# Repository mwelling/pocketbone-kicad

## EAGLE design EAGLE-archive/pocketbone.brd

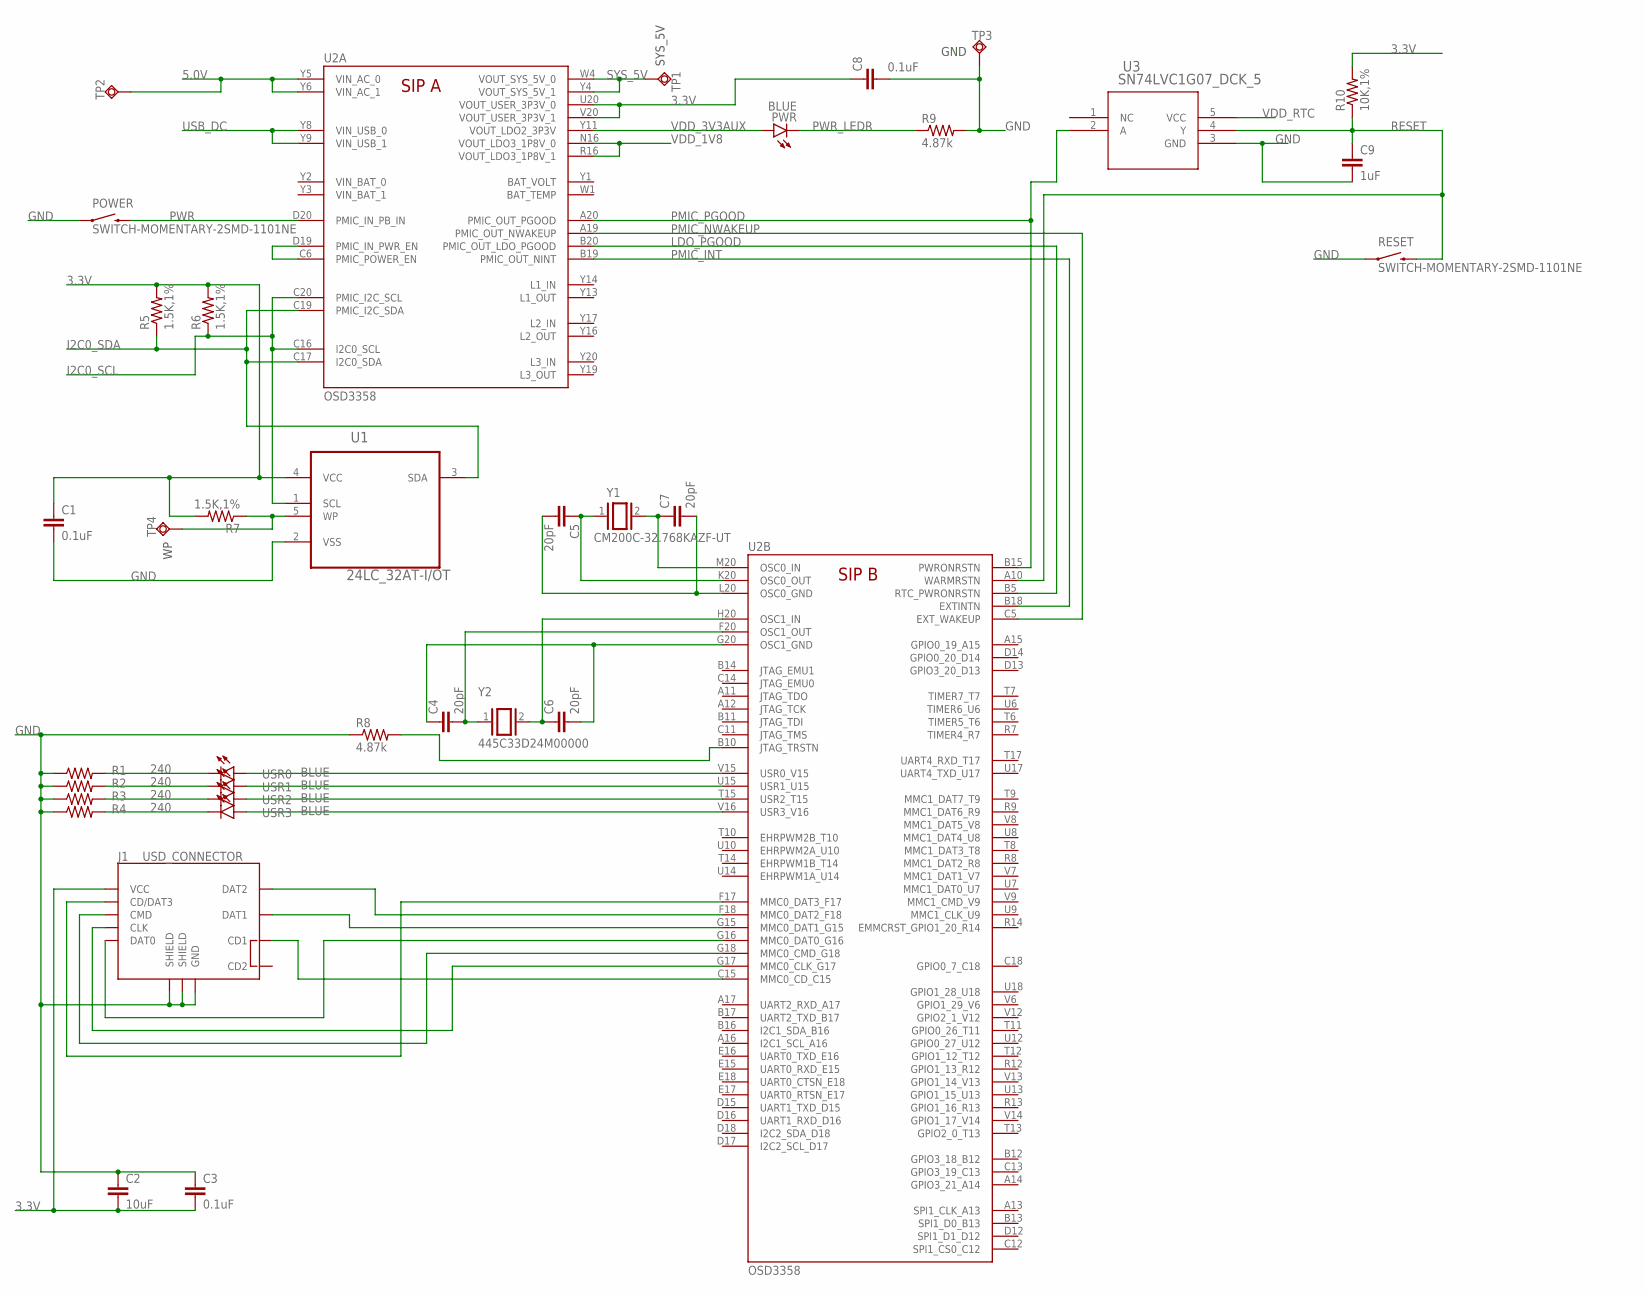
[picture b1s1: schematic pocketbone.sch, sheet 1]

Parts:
C1, C3, C8: 0.1uF; 0402-CAP
C2: 10uF; 0805
C4, C5, C6, C7: 20pF; 0402-CAP
C9: 1uF; 0402-CAP
J1: USD_CONNECTOR; MICRO-SD-SOCKET-PP
POWER: SWITCH-MOMENTARY-2SMD-1101NE; TACTILE-SWITCH-1101NE
PWR: BLUE; LED-0603
R1, R2, R3, R4: 240; 0402-RES
R5, R6, R7: 1.5K,1%; 0402-RES
R8, R9: 4.87k; 0402-RES
R10: 10K,1%; 0402-RES
RESET: SWITCH-MOMENTARY-2SMD-1101NE; TACTILE-SWITCH-1101NE
TP1, TP2, TP3, TP4: TPSQPAD1-17; P1-17
U1: 24LC_32AT-I/OT; SOT95P290X145-5N
U2: OSD3358
U3: SN74LVC1G07_DCK_5; DCK5
USR0, USR1, USR2, USR3: BLUE; LED-0603
Y1: CM200C-32.768KAZF-UT
Y2: 445C33D24M00000

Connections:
3.3V: C1.1, C2.2, C3.2, C8.1, J1.VCC, R5.2, R6.2, R7.2, R10.2, U1.4 (VCC), U2.U20 (VOUT_USER_3P3V_0), U2.V20 (VOUT_USER_3P3V_1); also elsewhere on the board
5.0V: TP2.TP, U2.Y5 (VIN_AC_0), U2.Y6 (VIN_AC_1); also elsewhere on the board
GND: C1.2, C2.1, C3.1, C8.2, C9.2, J1.GND, J1.GND1 (SHIELD), J1.GND3 (SHIELD), POWER.1, R1.1, R2.1, R3.1, R4.1, R8.1, R9.2, RESET.1, TP3.TP, U1.2 (VSS), U3.3 (GND); also elsewhere on the board
I2C0_SCL: R6.1, U1.1 (SCL), U2.C16 (I2C0_SCL), U2.C20 (PMIC_I2C_SCL)
I2C0_SDA: R5.1, U1.3 (SDA), U2.C17 (I2C0_SDA), U2.C19 (PMIC_I2C_SDA)
LDO_PGOOD: U2.B5 (RTC_PWRONRSTN), U2.B20 (PMIC_OUT_LDO_PGOOD)
unnamed: J1.CLK, U2.G17 (MMC0_CLK_G17)
unnamed: J1.CD/DAT3, U2.F17 (MMC0_DAT3_F17)
unnamed: U2.C6 (PMIC_POWER_EN), U2.D19 (PMIC_IN_PWR_EN)
unnamed: C7.1, U2.M20 (OSC0_IN), Y1.2
unnamed: C5.1, U2.K20 (OSC0_OUT), Y1.1
unnamed: R7.1, TP4.TP, U1.5 (WP)
unnamed: C5.2, C7.2, U2.L20 (OSC0_GND)
unnamed: C6.1, U2.H20 (OSC1_IN), Y2.2
unnamed: C4.2, U2.F20 (OSC1_OUT), Y2.1
unnamed: C4.1, C6.2, U2.G20 (OSC1_GND)
unnamed: R8.2, U2.B10 (JTAG_TRSTN)
unnamed: U2.V16 (USR3_V16), USR3.A
unnamed: U2.T15 (USR2_T15), USR2.A
unnamed: U2.U15 (USR1_U15), USR1.A
unnamed: U2.V15 (USR0_V15), USR0.A
unnamed: R1.2, USR0.C
unnamed: R2.2, USR1.C
unnamed: R3.2, USR2.C
unnamed: R4.2, USR3.C
unnamed: J1.DAT1, U2.G15 (MMC0_DAT1_G15)
unnamed: J1.CMD, U2.G18 (MMC0_CMD_G18)
unnamed: J1.CD1, U2.C15 (MMC0_CD_C15)
unnamed: J1.DAT0, U2.G16 (MMC0_DAT0_G16)
NTE: J1.DAT2, U2.F18 (MMC0_DAT2_F18)
PMIC_INT: U2.B18 (EXTINTN), U2.B19 (PMIC_OUT_NINT)
PMIC_NWAKEUP: U2.A19 (PMIC_OUT_NWAKEUP), U2.C5 (EXT_WAKEUP)
PMIC_PGOOD: U2.A20 (PMIC_OUT_PGOOD), U2.B15 (PWRONRSTN), U3.2 (A)
PWR: POWER.2, U2.D20 (PMIC_IN_PB_IN)
PWR_LEDR: PWR.C, R9.1
RESET: C9.1, R10.1, RESET.2, U2.A10 (WARMRSTN), U3.4 (Y)
SYS_5V: TP1.TP, U2.W4 (VOUT_SYS_5V_0), U2.Y4 (VOUT_SYS_5V_1); also elsewhere on the board
USB_DC: U2.Y8 (VIN_USB_0), U2.Y9 (VIN_USB_1); also elsewhere on the board
VDD_1V8: U2.N16 (VOUT_LDO3_1P8V_0), U2.R16 (VOUT_LDO3_1P8V_1); also elsewhere on the board
VDD_3V3AUX: PWR.A, U2.Y11 (VOUT_LDO2_3P3V)
VDD_RTC: U3.5 (VCC); also elsewhere on the board
VIN_BAT_0: U2.Y2 (VIN_BAT_0)
VIN_BAT_1: U2.Y3 (VIN_BAT_1)

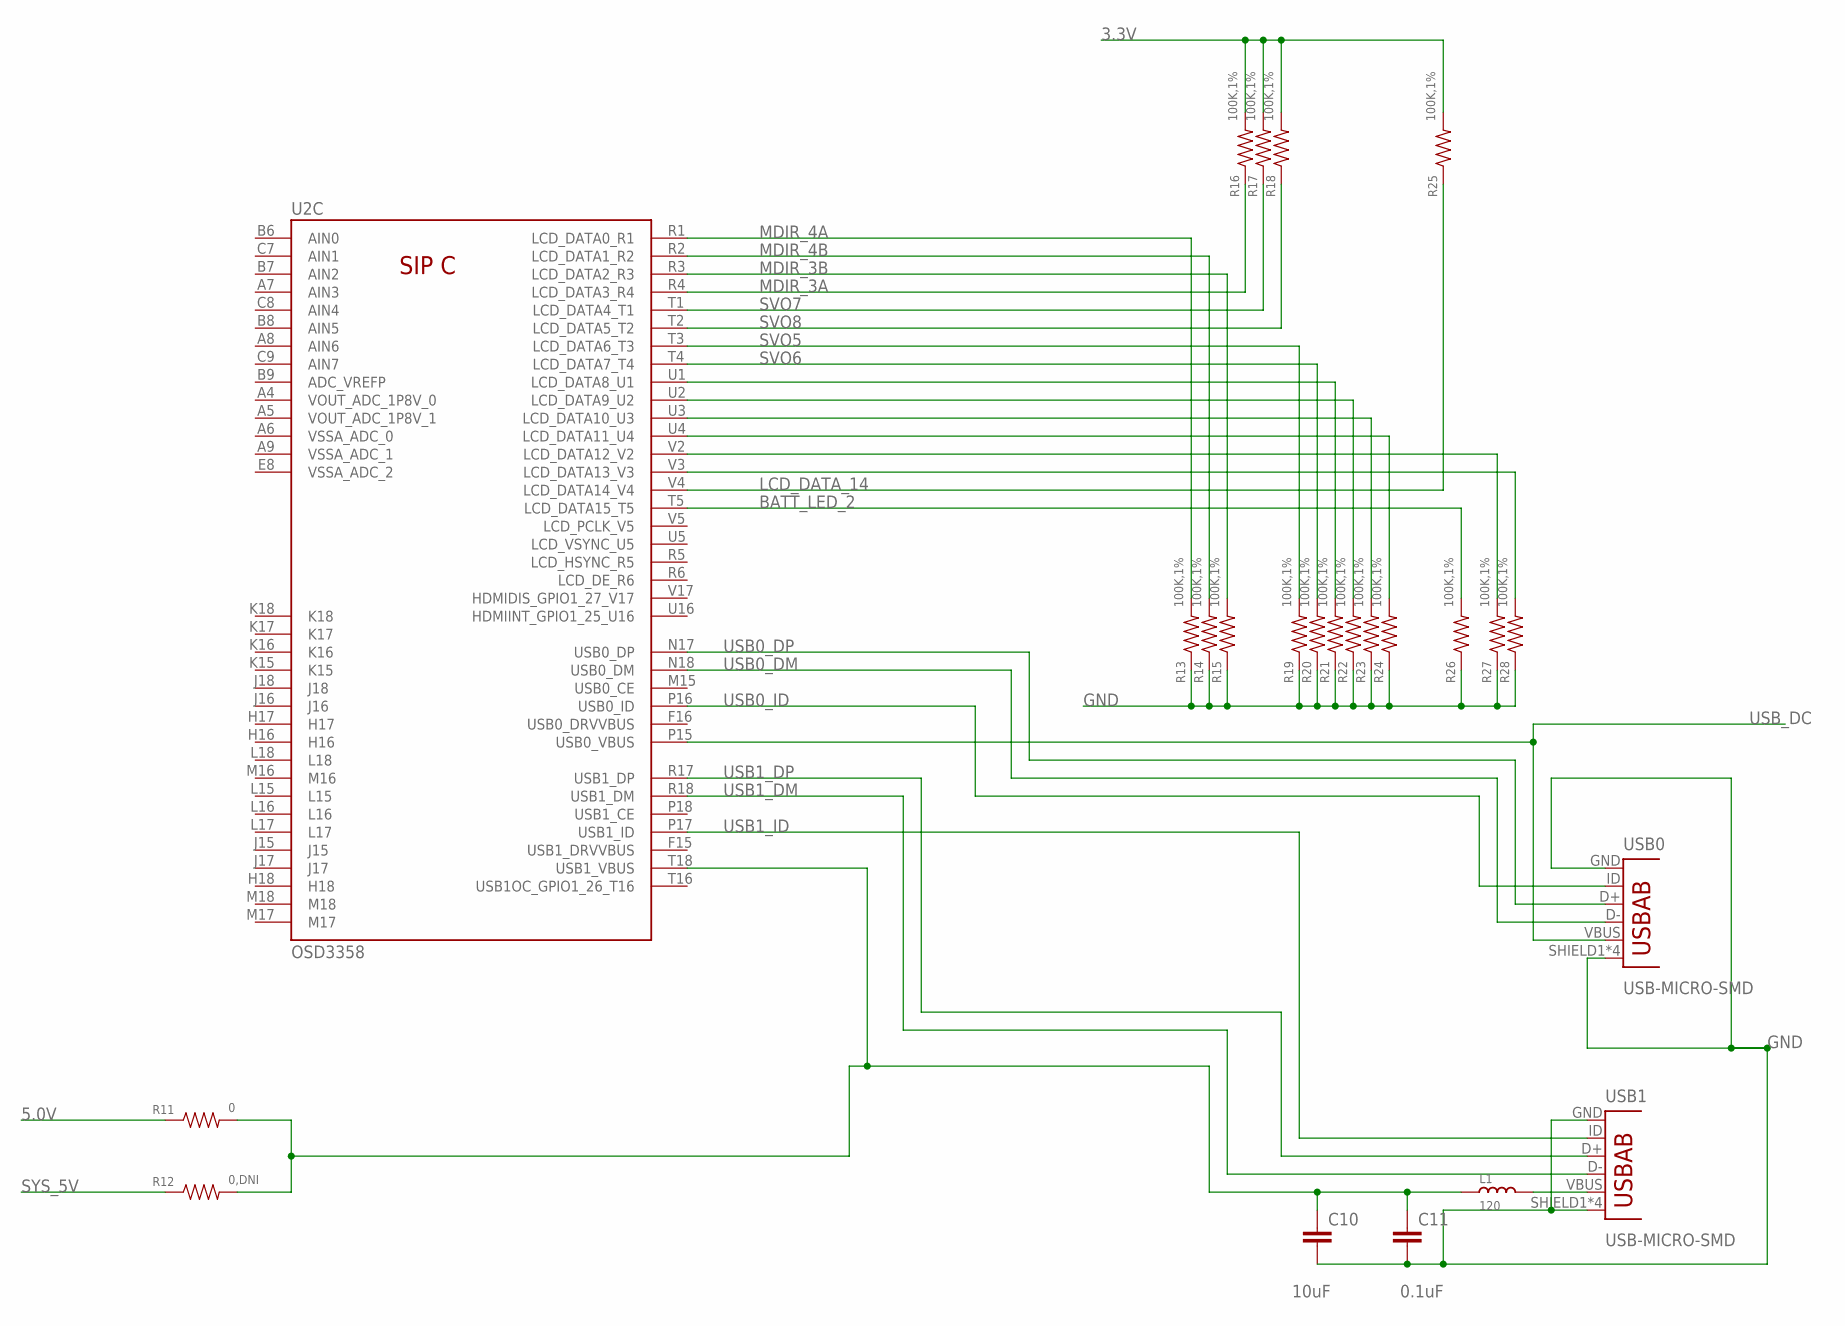
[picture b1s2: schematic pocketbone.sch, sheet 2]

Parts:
C10: 10uF; 0805
C11: 0.1uF; 0402-CAP
L1: 120; L0603
R11: 0; 0402-RES
R12: 0,DNI; 0402-RES
R13, R14, R15, R16, R17, R18, R19, R20, R21, R22, R23, R24, R25, R26, R27, R28: 100K,1%; 0402-RES
U2: OSD3358
USB0, USB1: USB-MICRO-SMD; USB-AB-MICRO-SMD

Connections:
3.3V: R16.2, R17.2, R18.2, R25.2; also elsewhere on the board
5.0V: R11.1; also elsewhere on the board
BATT_LED_2: R26.2, U2.T5 (LCD_DATA15_T5)
EQEP_1A: R27.2, U2.V2 (LCD_DATA12_V2)
EQEP_1B: R28.2, U2.V3 (LCD_DATA13_V3)
GND: C10.2, C11.2, R13.1, R14.1, R15.1, R19.1, R20.1, R21.1, R22.1, R23.1, R24.1, R26.1, R27.1, R28.1, USB0.GND, USB0.SHIELD1 (SHIELD), USB0.SHIELD2 (SHIELD), USB0.SHIELD3 (SHIELD), USB0.SHIELD4 (SHIELD), USB1.GND, USB1.SHIELD1 (SHIELD), USB1.SHIELD2 (SHIELD), USB1.SHIELD3 (SHIELD), USB1.SHIELD4 (SHIELD); also elsewhere on the board
LCD_DATA_14: R25.1, U2.V4 (LCD_DATA14_V4)
MDIR_2B: R24.2, U2.U4 (LCD_DATA11_U4)
MDIR_3A: R16.1, U2.R4 (LCD_DATA3_R4)
MDIR_3B: R15.2, U2.R3 (LCD_DATA2_R3)
MDIR_4A: R13.2, U2.R1 (LCD_DATA0_R1)
MDIR_4B: R14.2, U2.R2 (LCD_DATA1_R2)
unnamed: L1.2, USB1.VBUS
unnamed: C10.1, C11.1, L1.1, R11.2, R12.2, U2.T18 (USB1_VBUS)
SERVO_EN: R23.2, U2.U3 (LCD_DATA10_U3)
SVO5: R19.2, U2.T3 (LCD_DATA6_T3)
SVO6: R20.2, U2.T4 (LCD_DATA7_T4)
SVO7: R17.1, U2.T1 (LCD_DATA4_T1)
SVO8: R18.1, U2.T2 (LCD_DATA5_T2)
SYS_5V: R12.1; also elsewhere on the board
UART5_RX: R22.2, U2.U2 (LCD_DATA9_U2)
UART5_TX: R21.2, U2.U1 (LCD_DATA8_U1)
USB0_DM: U2.N18 (USB0_DM), USB0.D-
USB0_DP: U2.N17 (USB0_DP), USB0.D+
USB0_ID: U2.P16 (USB0_ID), USB0.ID (USBID)
USB1_DM: U2.R18 (USB1_DM), USB1.D-
USB1_DP: U2.R17 (USB1_DP), USB1.D+
USB1_ID: U2.P17 (USB1_ID), USB1.ID (USBID)
USB_DC: U2.P15 (USB0_VBUS), USB0.VBUS; also elsewhere on the board
VIN_BAT_0: U2.Y2 (VIN_BAT_0)
VIN_BAT_1: U2.Y3 (VIN_BAT_1)

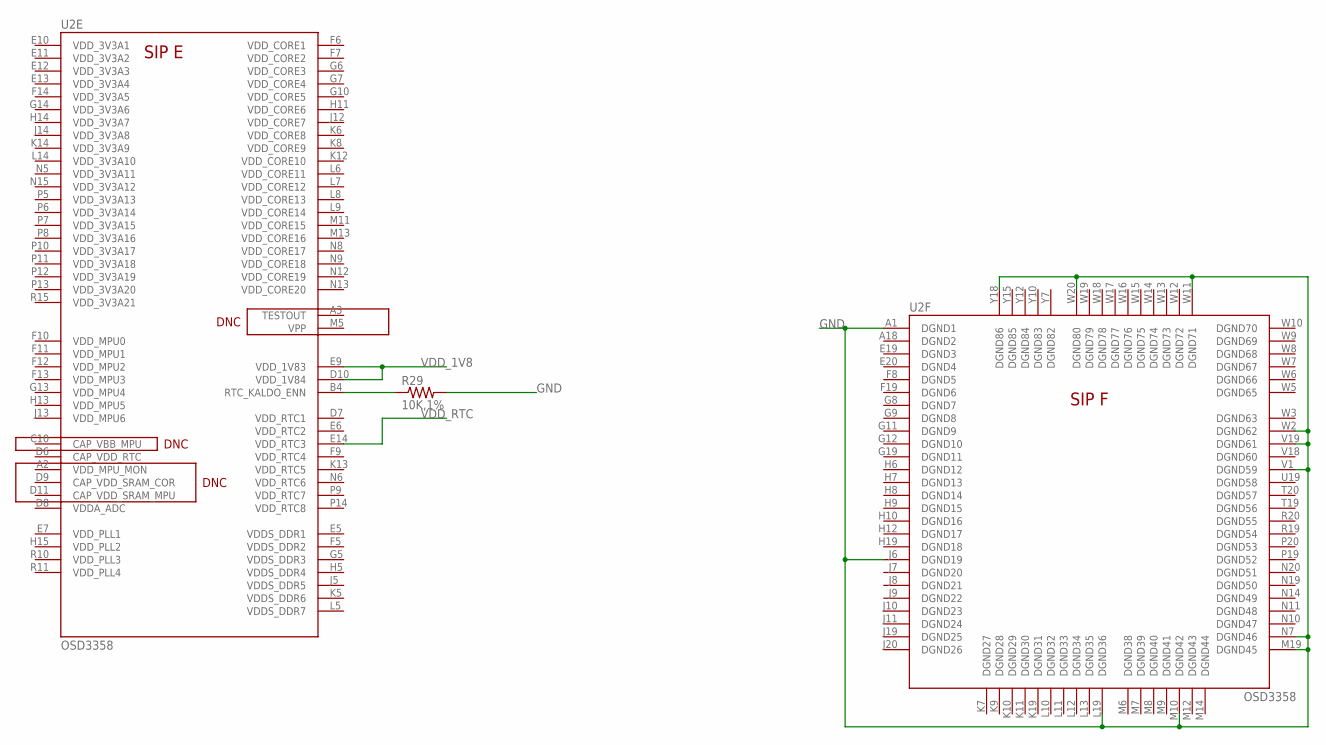
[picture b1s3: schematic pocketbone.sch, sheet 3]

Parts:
R29: 10K,1%; 0402-RES
U2: OSD3358

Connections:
GND: R29.2, U2.A1 (DGND1), U2.J6 (DGND19), U2.L19 (DGND36), U2.M10 (DGND42), U2.M19 (DGND45), U2.N7 (DGND46), U2.V1 (DGND59), U2.V19 (DGND61), U2.W2 (DGND62), U2.W11 (DGND71), U2.W20 (DGND80), U2.Y18 (DGND86); also elsewhere on the board
unnamed: R29.1, U2.B4 (RTC_KALDO_ENN)
VDD_1V8: U2.D10 (VDD_1V84), U2.E9 (VDD_1V83); also elsewhere on the board
VDD_RTC: U2.E14 (VDD_RTC3); also elsewhere on the board
VIN_BAT_0: U2.Y2 (VIN_BAT_0)
VIN_BAT_1: U2.Y3 (VIN_BAT_1)

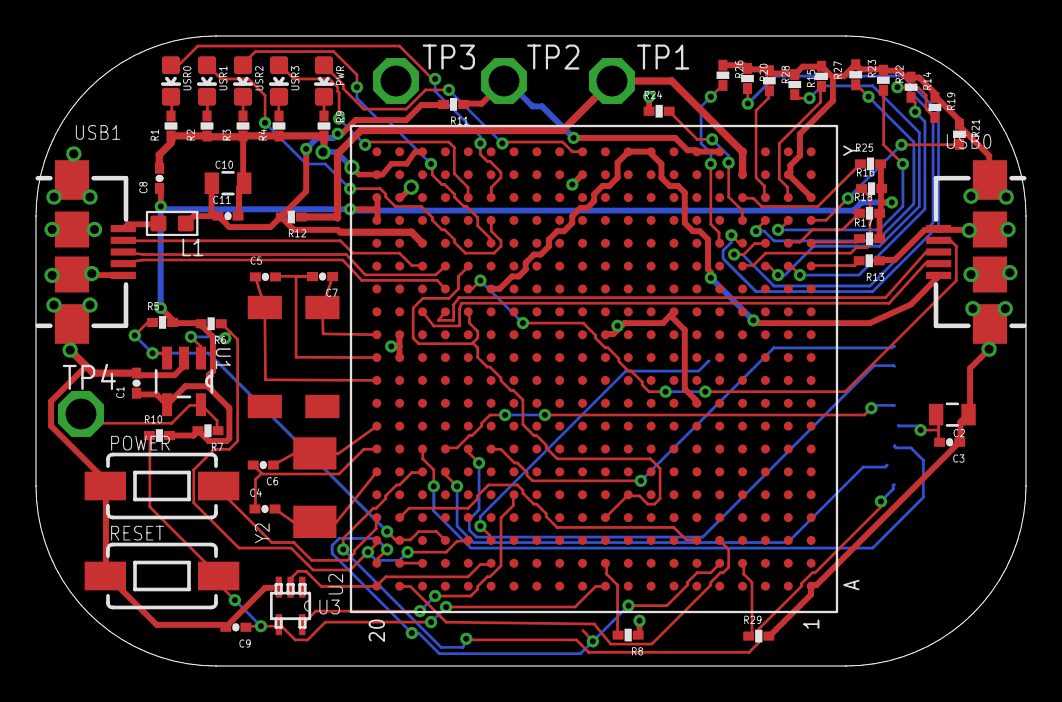
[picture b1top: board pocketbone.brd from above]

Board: 2 copper layers, 55.0 x 35.0 mm, 60 parts (1 on the bottom side), 66 nets.

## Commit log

2016-04-18 Add ground plane
2016-04-18 Consolidate library
    * Renumber parts
2016-04-18 Update some ref designators
2016-04-18 Rename USB connectors
2016-04-18 Resize some silkscreen
2016-04-18 Reposition components
2016-04-18 Routed USB1 DP/DN
2016-04-18 Routed USB0 DP/DN
2016-04-18 New rough placement
2016-04-18 Hack layout
2016-04-18 Adjusted resistors for 100% layout
2016-05-17 Connect microSD to 3.3V
2016-06-01 Tent vias
2016-11-22 Add README
2016-11-22 Add initial schematic conversion
    TODO:
    - Add buffer to drive reset with POR
    - Add header for expansion
    - Consider adding alternate power input
2016-11-22 Add schematic print for early review
2016-11-26 Schematic updates
    Adds microsd card
    Adds POR buffer
    Adds VBUS switch for Host mode on USB1
2016-11-26 Add updated schematic print for review
2016-11-27 Start placement of PCB
    TODO:
    Create footprint for microSD card.
    Choose appropriate ferrite bead footprint.
    Create footprint for crystals.
    Check patterns for all components.
2016-11-28 Few PCB updates
    Adds pattern for SD card and 24Mhz SMD crystal.
    Removes 32.768KHz crystal from design.
    Preliminary placement done.
    Need to add test points.
    All patterns need to be verified with specific components.
2016-11-28 Add 3D image to README for bling
2016-12-04 Add 10 pin IO header
2016-12-04 2 layer routing attempt
    TODO: Figure out proper USB routing with 2 layers.
2016-12-04 Update plots and README
2016-12-04 Update front of board 3d image
2017-01-18 Pull back routing and update placement
    The placement and footprint updated for USB.
    TODO: Attempt single sided population.
2017-02-02 Many PCB updates
    Updated the placement for single sided population.
    Switched boot mode selection resistors to arrays to save space.
    Switched expansion header to .1 inch (lichen pub compatible).
    Added battery connect similar to BBB.
2017-02-02 Update PDF with schematic changes
2017-02-09 Routing complete
    Battery header updated in schmatic.
    Plots and pictures updated.
    Ready for design review.
2017-02-09 Last minute tweaks
    This version is posted to OSHpark site for anyone to order.
    Order at your own risk.
2017-02-09 Update plots to the latest version
2017-02-10 Add OSHPark logo to the PCB and tweak the silk
    OSHPark sponsoring the first proto run. \o/
    https://oshpark.com/shared_projects/b7F6qftP
2017-02-10 Add an open hardware compatible license
    CERN OHL V1.2
2017-02-13 Updated Footprint and Schematic Librarys
    The Paths of the USB and SOT Footprints pointed to local Directorys on
    your HDD instead of the Project Folder
2017-03-01 Move EAGLE files to a subdirectory
2017-03-01 Remove EAGLE files
2017-03-01 Remove old .gitignore
2017-03-19 o Add Python script that can generate fabbing files from the command line. o Add Makefile that makes use of it: just calling 'make' will create a zip file with the necessary layers. o Send kicad_pcb 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
2017-03-23 o Limit changes in PCB file to only include the %%gitversion%% change.
2017-03-23 o OshPark only successfully recongizes the file names if EdgeCuts is named Edge_Cuts, so renmae that file.
2018-10-02 Testing KiCAD 5 port

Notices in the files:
parts and their libraries:
SparkFun-Electromechanical: Licensing: Creative Commons ShareAlike 4.0 International - https://creativecommons.org/licenses/by-sa/4.0
